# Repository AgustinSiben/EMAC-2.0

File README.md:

# EMAC-2.0
En este repositorio se encuentra contenido todo lo relacionado a la versión 2.0 del adquisidor de datos para EMAC (Estación de monitoreo ambiental costera)

Este repositorio se encuentra en desarrollo, se subiran las actualizaciones a medida que se avance en el mismo.

Ante cualquier consulta envíe un mail a la dirección: agustinsiben@gmail.com

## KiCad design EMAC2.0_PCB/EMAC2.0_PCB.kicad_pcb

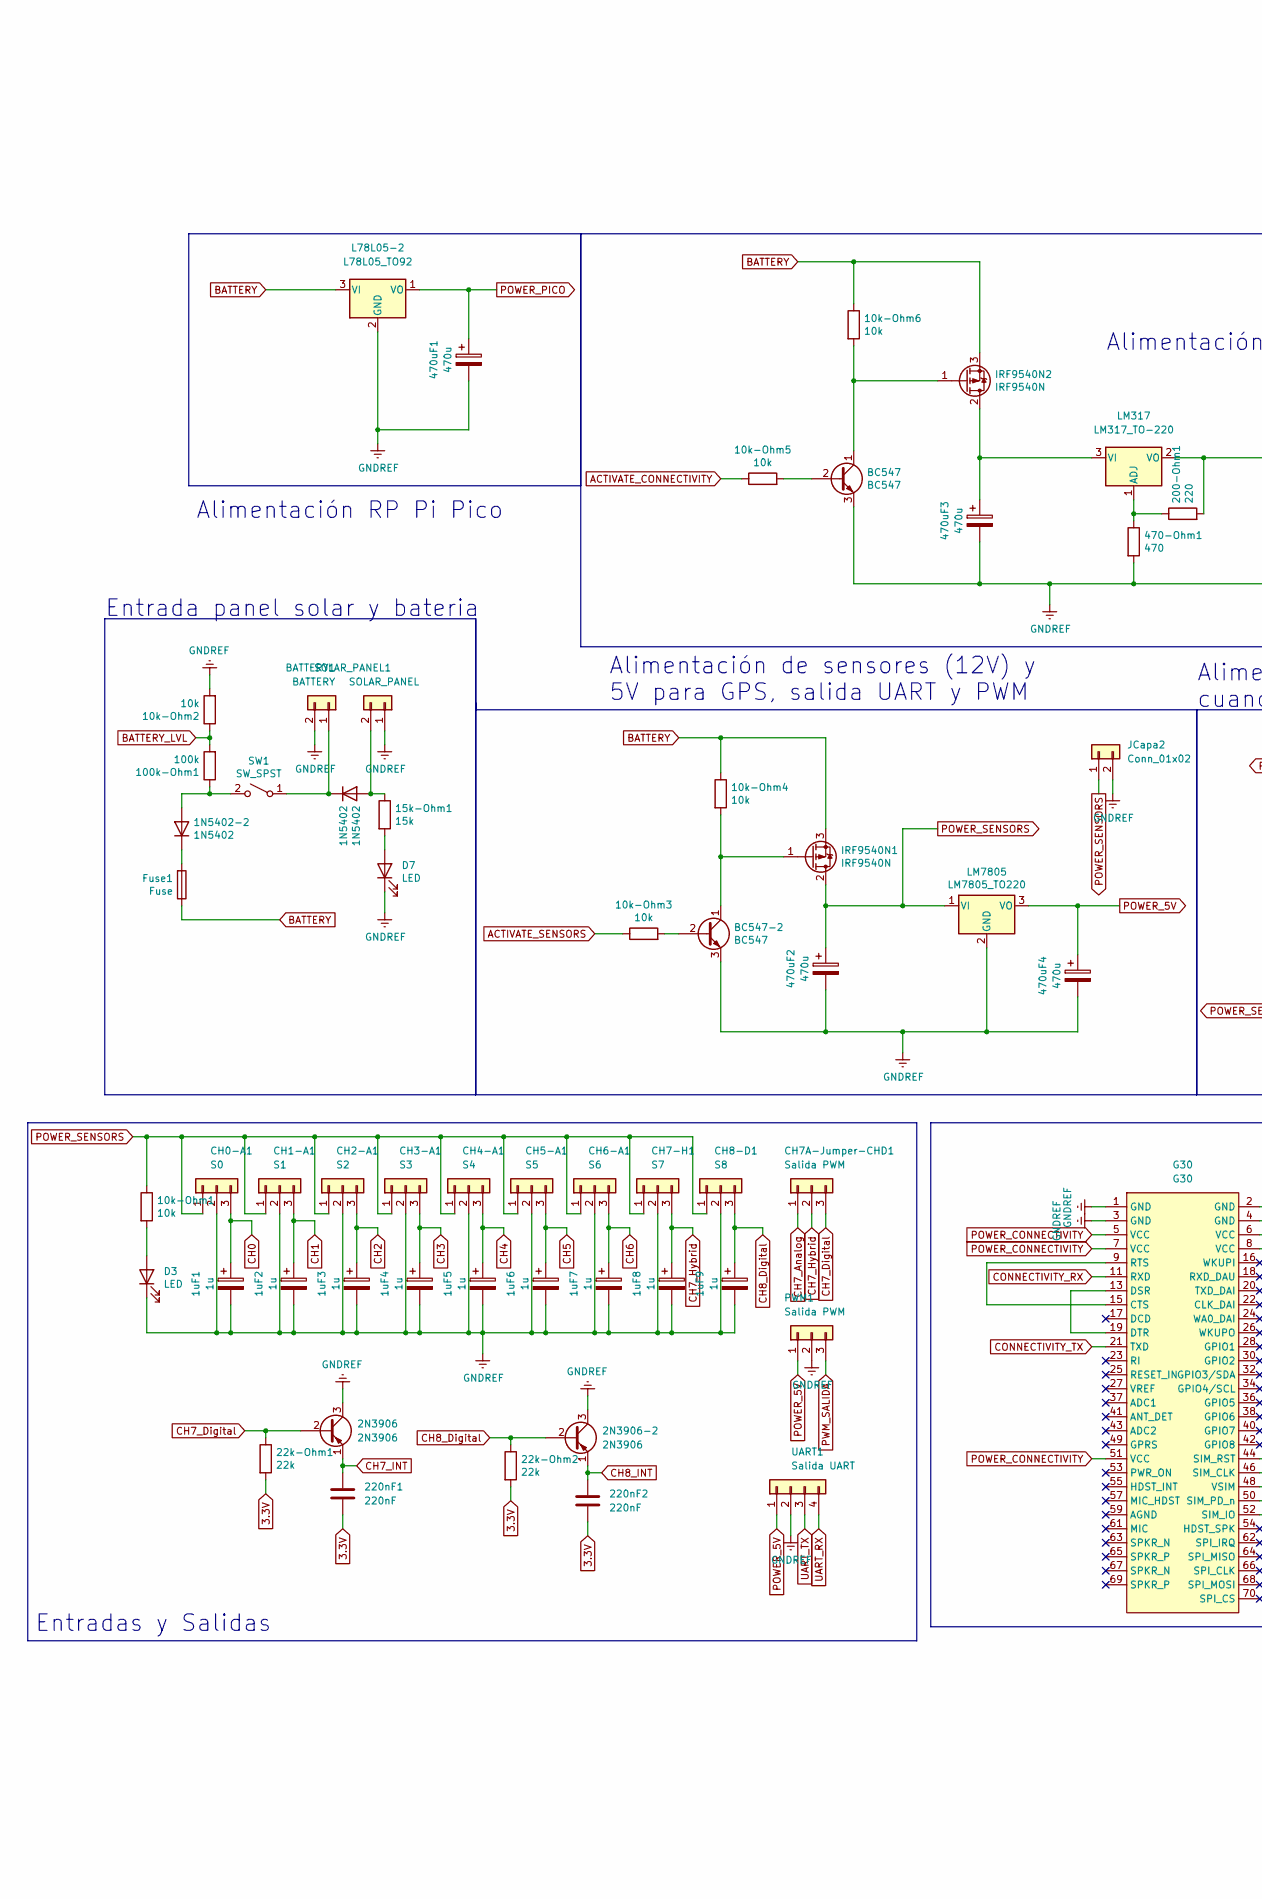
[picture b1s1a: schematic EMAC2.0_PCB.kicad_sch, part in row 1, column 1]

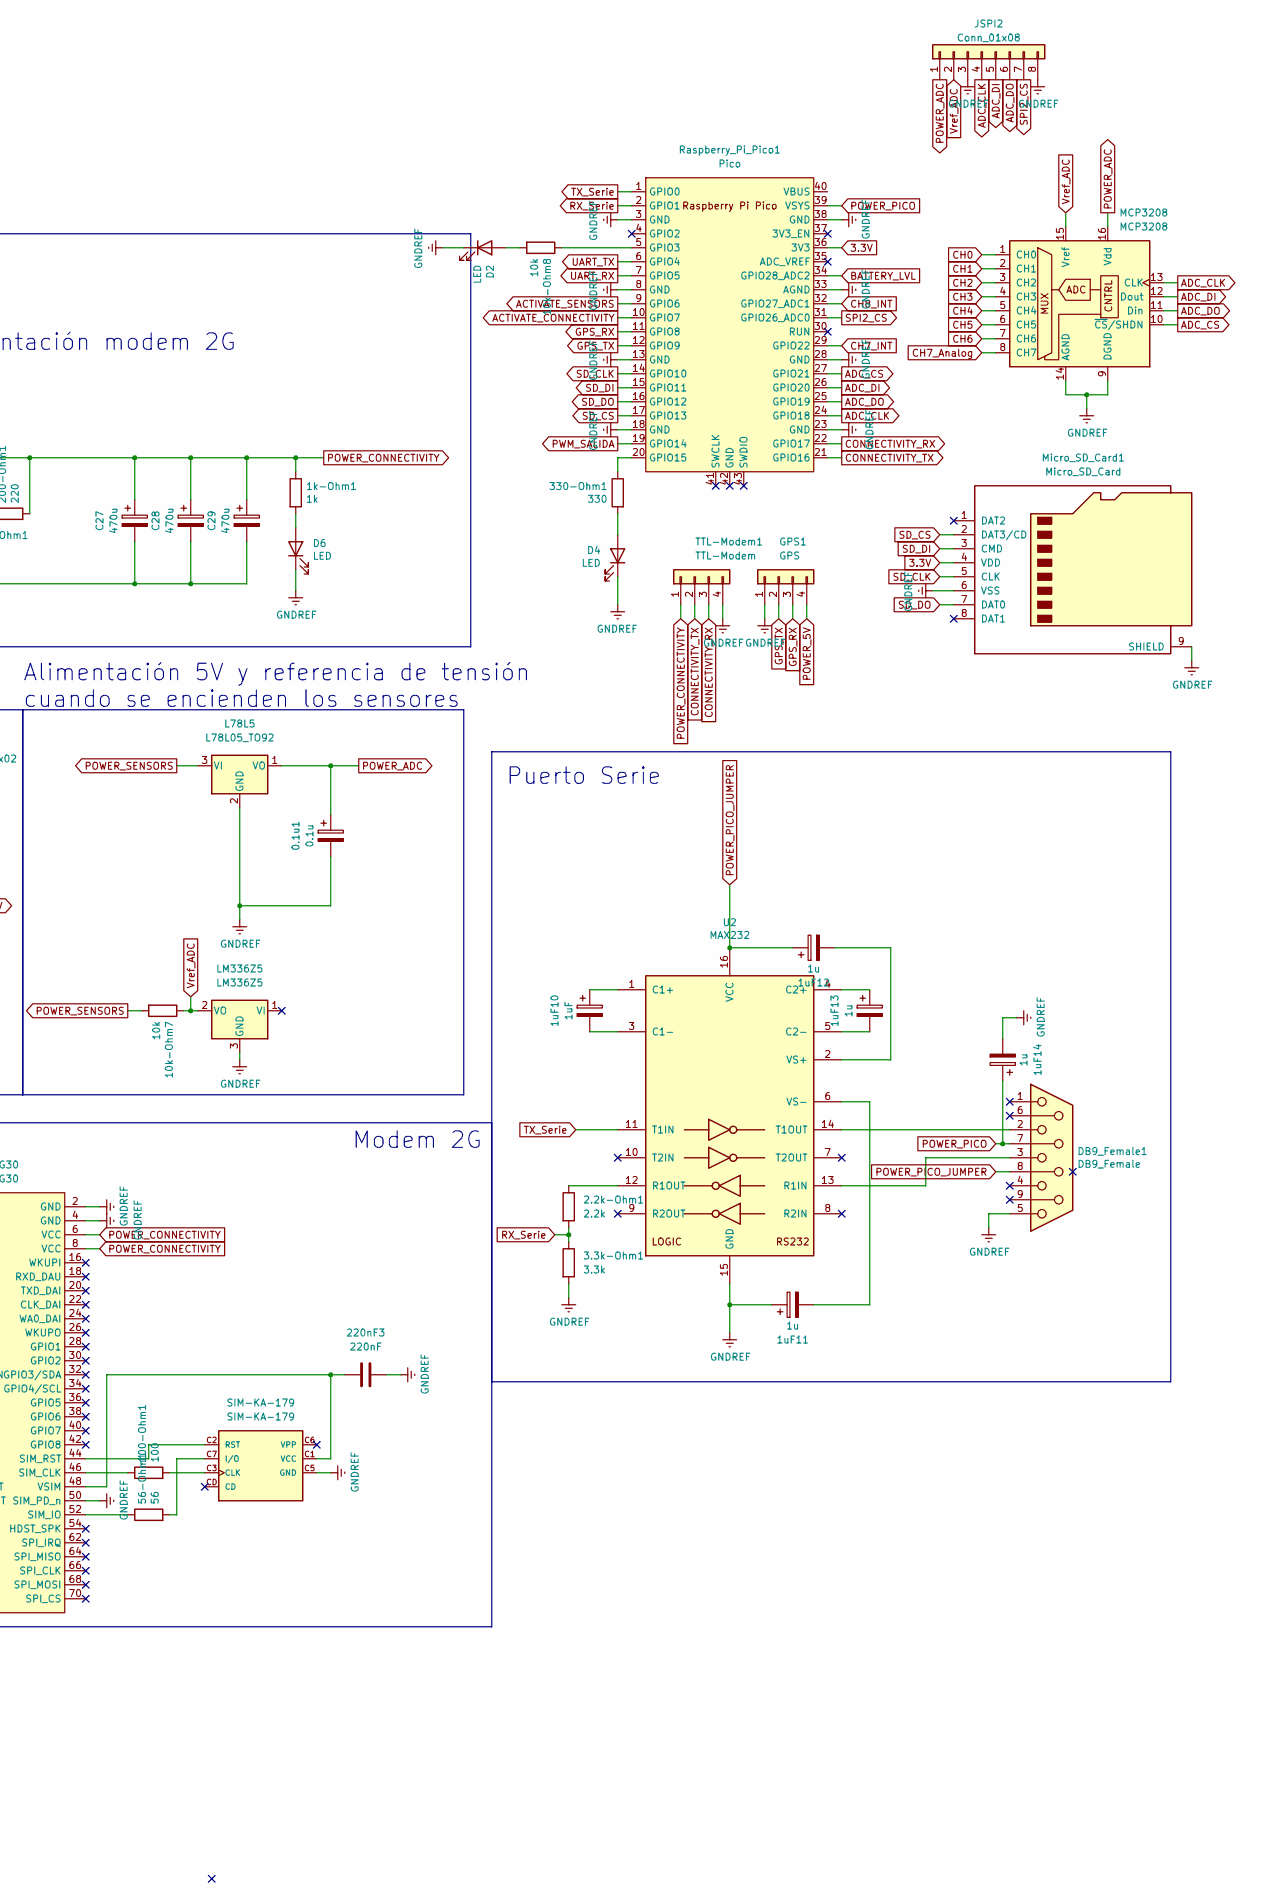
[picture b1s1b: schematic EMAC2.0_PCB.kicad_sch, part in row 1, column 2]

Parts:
0.1u1: 0.1u; CP_Radial_D5.0mm_P2.50mm
1N5402, 1N5402-2: 1N5402; D_DO-201AD_P15.24mm_Horizontal
1k-Ohm1: 1k; R_Axial_DIN0207_L6.3mm_D2.5mm_P10.16mm_Horizontal
1uF1, 1uF2, 1uF3, 1uF4, 1uF5, 1uF6, 1uF7, 1uF8, 1uF9, 1uF11, 1uF12, 1uF13, 1uF14: 1u; CP_Radial_D5.0mm_P2.50mm
1uF10: 1uF; CP_Radial_D5.0mm_P2.50mm
2.2k-Ohm1: 2.2k; R_Axial_DIN0207_L6.3mm_D2.5mm_P10.16mm_Horizontal
2N3906, 2N3906-2: 2N3906; TO-92_Inline_Wide
3.3k-Ohm1: 3.3k; R_Axial_DIN0207_L6.3mm_D2.5mm_P10.16mm_Horizontal
10k-Ohm1, 10k-Ohm2, 10k-Ohm3, 10k-Ohm4, 10k-Ohm5, 10k-Ohm6, 10k-Ohm7, 10k-Ohm8: 10k; R_Axial_DIN0207_L6.3mm_D2.5mm_P10.16mm_Horizontal
15k-Ohm1: 15k; R_Axial_DIN0207_L6.3mm_D2.5mm_P10.16mm_Horizontal
22k-Ohm1, 22k-Ohm2: 22k; R_Axial_DIN0207_L6.3mm_D2.5mm_P10.16mm_Horizontal
56-Ohm1: 56; R_Axial_DIN0207_L6.3mm_D2.5mm_P10.16mm_Horizontal
100-Ohm1: 100; R_Axial_DIN0207_L6.3mm_D2.5mm_P10.16mm_Horizontal
100k-Ohm1: 100k; R_Axial_DIN0207_L6.3mm_D2.5mm_P10.16mm_Horizontal
200-Ohm1: 220; R_Axial_DIN0207_L6.3mm_D2.5mm_P10.16mm_Horizontal
220nF1, 220nF2, 220nF3: 220nF; C_Disc_D5.1mm_W3.2mm_P5.00mm
330-Ohm1: 330; R_Axial_DIN0207_L6.3mm_D2.5mm_P10.16mm_Horizontal
470-Ohm1: 470; R_Axial_DIN0207_L6.3mm_D2.5mm_P10.16mm_Horizontal
470uF1, 470uF2, 470uF3, 470uF4: 470u; CP_Radial_D8.0mm_P5.00mm
BATTERY1: BATTERY; PhoenixContact_MSTBA_2,5_2-G-5,08_1x02_P5.08mm_Horizontal_B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
BC547, BC547-2: BC547; TO-92_Inline_Wide
C27, C28, C29: 470u; CP_Radial_D8.0mm_P5.00mm
CH0-A1: S0; PhoenixContact_MSTBA_2,5_3-G-5,08_1x03_P5.08mm_Horizontal_B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
CH1-A1: S1; PhoenixContact_MSTBA_2,5_3-G-5,08_1x03_P5.08mm_Horizontal_B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
CH2-A1: S2; PhoenixContact_MSTBA_2,5_3-G-5,08_1x03_P5.08mm_Horizontal_B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
CH3-A1: S3; PhoenixContact_MSTBA_2,5_3-G-5,08_1x03_P5.08mm_Horizontal_B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
CH4-A1: S4; PhoenixContact_MSTBA_2,5_3-G-5,08_1x03_P5.08mm_Horizontal_B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
CH5-A1: S5; PhoenixContact_MSTBA_2,5_3-G-5,08_1x03_P5.08mm_Horizontal_B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
CH6-A1: S6; PhoenixContact_MSTBA_2,5_3-G-5,08_1x03_P5.08mm_Horizontal_B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
CH7-H1: S7; PhoenixContact_MSTBA_2,5_3-G-5,08_1x03_P5.08mm_Horizontal_B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
CH7A-Jumper-CHD1: Salida PWM; PinHeader_1x03_P2.54mm_Vertical
CH8-D1: S8; PhoenixContact_MSTBA_2,5_3-G-5,08_1x03_P5.08mm_Horizontal_B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
D2, D3, D4, D6, D7: LED; LED_D4.0mm
DB9_Female1: DB9_Female; DSUB-9_Female_Horizontal_P2.77x2.84mm_EdgePinOffset4.94mm_H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
Fuse1: Fuse; 20x5
G30: G30; Molex_SlimStack_52991-0708_2x35_P0.50mm_Vertical
GPS1: GPS; PinHeader_1x04_P2.54mm_Vertical
IRF9540N1, IRF9540N2: IRF9540N; TO-220-3_Vertical
JCapa2: Conn_01x02; PinHeader_1x02_P2.54mm_Vertical
JSPI2: Conn_01x08; PinHeader_1x08_P2.54mm_Vertical
L78L5, L78L05-2: L78L05_TO92; TO-92_Inline_Wide
LM317: LM317_TO-220; TO-220-3_Vertical
LM336Z5: LM336Z5; TO-92_Inline_Wide
LM7805: LM7805_TO220; TO-220-3_Vertical
MCP3208: MCP3208; DIP-16_W7.62mm_Socket
Micro_SD_Card1: Micro_SD_Card; GCT-MEM2055-00-190-01-A
PWM1: Salida PWM; PhoenixContact_MSTBA_2,5_3-G-5,08_1x03_P5.08mm_Horizontal_B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
Raspberry_Pi_Pico1: Pico; RPi_Pico_SMD_TH
SIM-KA-179: SIM-KA-179; GCT_SIM7100-6-1-15-00-A_REVC; PARTREV C
SOLAR_PANEL1: SOLAR_PANEL; PhoenixContact_MSTBA_2,5_2-G-5,08_1x02_P5.08mm_Horizontal_B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
SW1: SW_SPST; SolderWire-0.75sqmm_1x02_P7mm_D1.25mm_OD3.5mm
TTL-Modem1: TTL-Modem; PinHeader_1x04_P2.54mm_Vertical
U2: MAX232; SOIC-16_3.9x9.9mm_P1.27mm
UART1: Salida UART; PhoenixContact_MSTBA_2,5_4-G-5,08_1x04_P5.08mm_Horizontal_B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

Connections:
3.3V: 22k-Ohm1.2, 22k-Ohm2.2, 220nF1.2, 220nF2.2, Micro_SD_Card1.4 (VDD), Raspberry_Pi_Pico1.36 (3V3)
ACTIVATE_CONNECTIVITY: 10k-Ohm5.1, Raspberry_Pi_Pico1.10 (GPIO7)
ACTIVATE_SENSORS: 10k-Ohm3.1, Raspberry_Pi_Pico1.9 (GPIO6)
ADC_CLK: JSPI2.4, MCP3208.13 (CLK), Raspberry_Pi_Pico1.24 (GPIO18)
ADC_CS: MCP3208.10 (~CS/SHDN), Raspberry_Pi_Pico1.27 (GPIO21)
ADC_DI: JSPI2.5, MCP3208.12 (Dout), Raspberry_Pi_Pico1.26 (GPIO20)
ADC_DO: JSPI2.6, MCP3208.11 (Din), Raspberry_Pi_Pico1.25 (GPIO19)
BATTERY: 10k-Ohm4.1, 10k-Ohm6.1, Fuse1.1, IRF9540N1.3 (S), IRF9540N2.3 (S), L78L05-2.3 (VI)
BATTERY_LVL: 10k-Ohm2.1, 100k-Ohm1.2, Raspberry_Pi_Pico1.34 (GPIO28_ADC2)
CH0: 1uF1.1, CH0-A1.3, MCP3208.1 (CH0)
CH1: 1uF2.1, CH1-A1.3, MCP3208.2 (CH1)
CH2: 1uF3.1, CH2-A1.3, MCP3208.3 (CH2)
CH3: 1uF4.1, CH3-A1.3, MCP3208.4 (CH3)
CH4: 1uF5.1, CH4-A1.3, MCP3208.5 (CH4)
CH5: 1uF6.1, CH5-A1.3, MCP3208.6 (CH5)
CH6: 1uF7.1, CH6-A1.3, MCP3208.7 (CH6)
CH7_Analog: CH7A-Jumper-CHD1.1, MCP3208.8 (CH7)
CH7_Digital: 2N3906.2 (B), 22k-Ohm1.1, CH7A-Jumper-CHD1.3
CH7_Hybrid: 1uF8.1, CH7-H1.3, CH7A-Jumper-CHD1.2
CH7_INT: 2N3906.1 (E), 220nF1.1, Raspberry_Pi_Pico1.29 (GPIO22)
CH8_Digital: 1uF9.1, 2N3906-2.2 (B), 22k-Ohm2.1, CH8-D1.3
CH8_INT: 2N3906-2.1 (E), 220nF2.1, Raspberry_Pi_Pico1.32 (GPIO27_ADC1)
CONNECTIVITY_RX: G30.11 (RXD), Raspberry_Pi_Pico1.22 (GPIO17), TTL-Modem1.3
CONNECTIVITY_TX: G30.21 (TXD), Raspberry_Pi_Pico1.21 (GPIO16), TTL-Modem1.2
GNDREF: 0.1u1.2, 1uF1.2, 1uF2.2, 1uF3.2, 1uF4.2, 1uF5.2, 1uF6.2, 1uF7.2, 1uF8.2, 1uF9.2, 1uF11.1, 1uF14.2, 2N3906.3 (C), 2N3906-2.3 (C), 3.3k-Ohm1.2, 10k-Ohm2.2, 220nF3.1, 470-Ohm1.2, 470uF1.2, 470uF2.2, 470uF3.2, 470uF4.2, BATTERY1.2, BC547.3 (E), BC547-2.3 (E), C27.2, C28.2, C29.2, CH0-A1.2, CH1-A1.2, CH2-A1.2, CH3-A1.2, CH4-A1.2, CH5-A1.2, CH6-A1.2, CH7-H1.2, CH8-D1.2, D2.1 (K), D3.1 (K), D4.1 (K), D6.1 (K), D7.1 (K), DB9_Female1.5, G30.1 (GND), G30.2 (GND), G30.3 (GND), G30.4 (GND), G30.50 (SIM_PD_n), GPS1.1, JCapa2.2, JSPI2.3, JSPI2.8, L78L5.2 (GND), L78L05-2.2 (GND), LM336Z5.3 (GND), LM7805.2 (GND), MCP3208.9 (DGND), MCP3208.14 (AGND), Micro_SD_Card1.6 (VSS), Micro_SD_Card1.9 (SHIELD), PWM1.2, Raspberry_Pi_Pico1.3 (GND), Raspberry_Pi_Pico1.8 (GND), Raspberry_Pi_Pico1.13 (GND), Raspberry_Pi_Pico1.18 (GND), Raspberry_Pi_Pico1.23 (GND), Raspberry_Pi_Pico1.28 (GND), Raspberry_Pi_Pico1.33 (AGND), Raspberry_Pi_Pico1.38 (GND), SIM-KA-179.C5 (GND), SOLAR_PANEL1.1, TTL-Modem1.4, U2.15 (GND), UART1.2
GPS_RX: GPS1.3, Raspberry_Pi_Pico1.11 (GPIO8)
GPS_TX: GPS1.2, Raspberry_Pi_Pico1.12 (GPIO9)
unnamed: 1N5402-2.1 (K), Fuse1.2
unnamed: 1N5402.1 (K), BATTERY1.1, SW1.1 (A)
unnamed: 1k-Ohm1.2, D6.2 (A)
unnamed: 1uF10.1, U2.1 (C1+)
unnamed: 1uF10.2, U2.3 (C1-)
unnamed: 1uF11.2, U2.6 (VS-)
unnamed: 1uF12.2, U2.2 (VS+)
unnamed: 1uF13.1, U2.4 (C2+)
unnamed: 1uF13.2, U2.5 (C2-)
unnamed: 2.2k-Ohm1.1, U2.12 (R1OUT)
unnamed: 10k-Ohm1.2, D3.2 (A)
unnamed: 10k-Ohm3.2, BC547-2.2 (B)
unnamed: 10k-Ohm4.2, BC547-2.1 (C), IRF9540N1.1 (G)
unnamed: 10k-Ohm5.2, BC547.2 (B)
unnamed: 10k-Ohm6.2, BC547.1 (C), IRF9540N2.1 (G)
unnamed: 10k-Ohm8.1, Raspberry_Pi_Pico1.5 (GPIO3)
unnamed: 10k-Ohm8.2, D2.2 (A)
unnamed: 1N5402.2 (A), 15k-Ohm1.1, SOLAR_PANEL1.2
unnamed: 15k-Ohm1.2, D7.2 (A)
unnamed: 56-Ohm1.1, G30.52 (SIM_IO)
unnamed: 56-Ohm1.2, SIM-KA-179.C7 (I/O)
unnamed: 100-Ohm1.1, G30.46 (SIM_CLK)
unnamed: 100-Ohm1.2, SIM-KA-179.C3 (CLK)
unnamed: 1N5402-2.2 (A), 100k-Ohm1.1, SW1.2 (B)
unnamed: 200-Ohm1.1, 470-Ohm1.1, LM317.1 (ADJ)
unnamed: 220nF3.2, G30.48 (VSIM), SIM-KA-179.C1 (VCC)
unnamed: 330-Ohm1.1, Raspberry_Pi_Pico1.20 (GPIO15)
unnamed: 330-Ohm1.2, D4.2 (A)
unnamed: 470uF3.1, IRF9540N2.2 (D), LM317.3 (VI)
unnamed: DB9_Female1.2, U2.14 (T1OUT)
unnamed: DB9_Female1.3, U2.13 (R1IN)
unnamed: G30.13 (DSR), G30.19 (DTR)
unnamed: G30.9 (RTS), G30.15 (CTS)
unnamed: G30.44 (SIM_RST), SIM-KA-179.C2 (RST)
POWER_5V: 470uF4.1, GPS1.4, LM7805.3 (VO), PWM1.1, UART1.1
POWER_ADC: 0.1u1.1, JSPI2.1, L78L5.1 (VO), MCP3208.16 (Vdd)
POWER_CONNECTIVITY: 1k-Ohm1.1, 200-Ohm1.2, C27.1, C28.1, C29.1, G30.5 (VCC), G30.6 (VCC), G30.7 (VCC), G30.8 (VCC), G30.51 (VCC), LM317.2 (VO), TTL-Modem1.1
POWER_PICO: 1uF14.1, 470uF1.1, DB9_Female1.7, L78L05-2.1 (VO), Raspberry_Pi_Pico1.39 (VSYS)
POWER_PICO_JUMPER: 1uF12.1, DB9_Female1.8, U2.16 (VCC)
POWER_SENSORS: 10k-Ohm1.1, 10k-Ohm7.2, 470uF2.1, CH0-A1.1, CH1-A1.1, CH2-A1.1, CH3-A1.1, CH4-A1.1, CH5-A1.1, CH6-A1.1, CH7-H1.1, CH8-D1.1, IRF9540N1.2 (D), JCapa2.1, L78L5.3 (VI), LM7805.1 (VI)
PWM_SALIDA: PWM1.3, Raspberry_Pi_Pico1.19 (GPIO14)
RX_Serie: 2.2k-Ohm1.2, 3.3k-Ohm1.1, Raspberry_Pi_Pico1.2 (GPIO1)
SD_CLK: Micro_SD_Card1.5 (CLK), Raspberry_Pi_Pico1.14 (GPIO10)
SD_CS: Micro_SD_Card1.2 (DAT3/CD), Raspberry_Pi_Pico1.17 (GPIO13)
SD_DI: Micro_SD_Card1.3 (CMD), Raspberry_Pi_Pico1.15 (GPIO11)
SD_DO: Micro_SD_Card1.7 (DAT0), Raspberry_Pi_Pico1.16 (GPIO12)
SPI2_CS: JSPI2.7, Raspberry_Pi_Pico1.31 (GPIO26_ADC0)
TX_Serie: Raspberry_Pi_Pico1.1 (GPIO0), U2.11 (T1IN)
UART_RX: Raspberry_Pi_Pico1.7 (GPIO5), UART1.4
UART_TX: Raspberry_Pi_Pico1.6 (GPIO4), UART1.3
Vref_ADC: 10k-Ohm7.1, JSPI2.2, LM336Z5.2 (VO), MCP3208.15 (Vref)

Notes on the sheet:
Modem 2G
Alimentación modem 2G
Alimentación 5V y referencia de tensión cuando se encienden los sensores
Entradas y Salidas
Entrada panel solar y bateria
Alimentación RP Pi Pico
Puerto Serie
Alimentación de sensores (12V) y 5V para GPS, salida UART y PWM

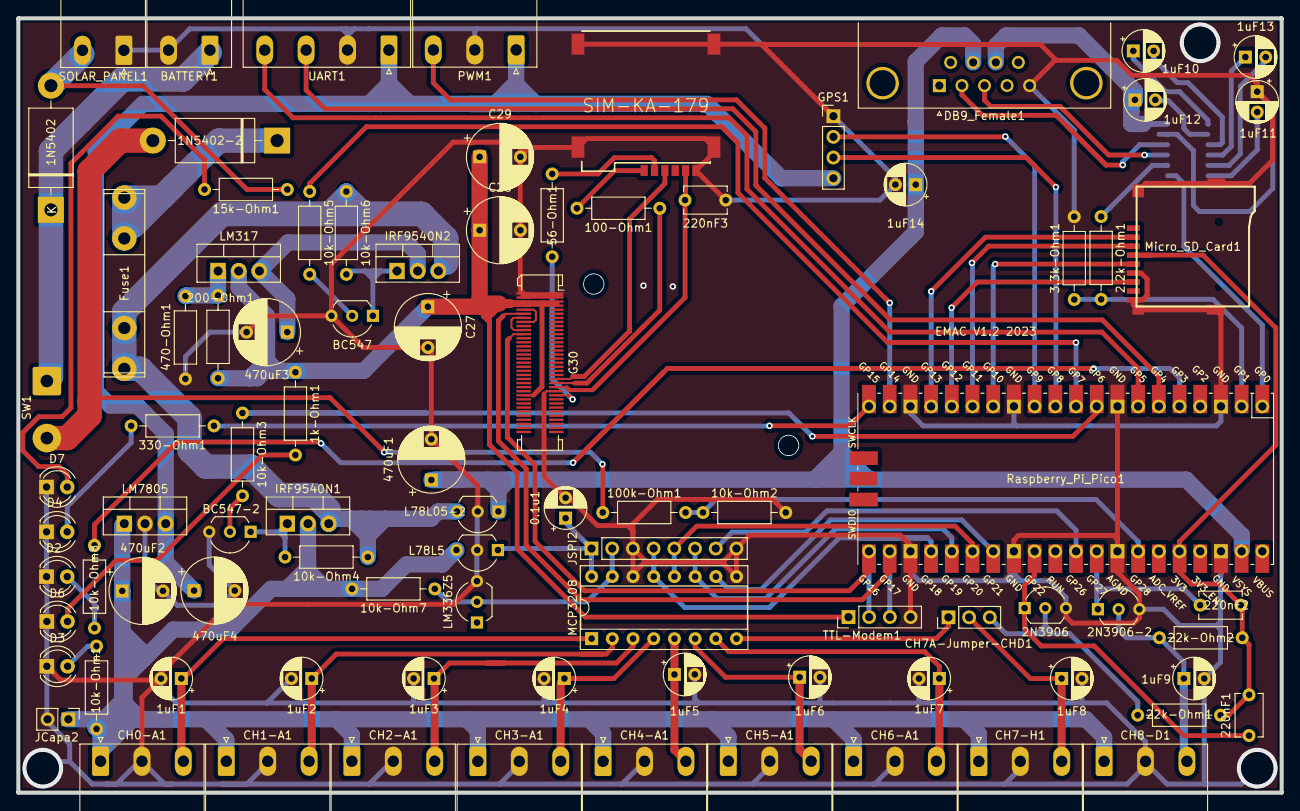
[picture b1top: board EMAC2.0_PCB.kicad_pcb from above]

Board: 2 copper layers, 155.0 x 95.0 mm, 90 parts (1 on the bottom side), 78 nets.

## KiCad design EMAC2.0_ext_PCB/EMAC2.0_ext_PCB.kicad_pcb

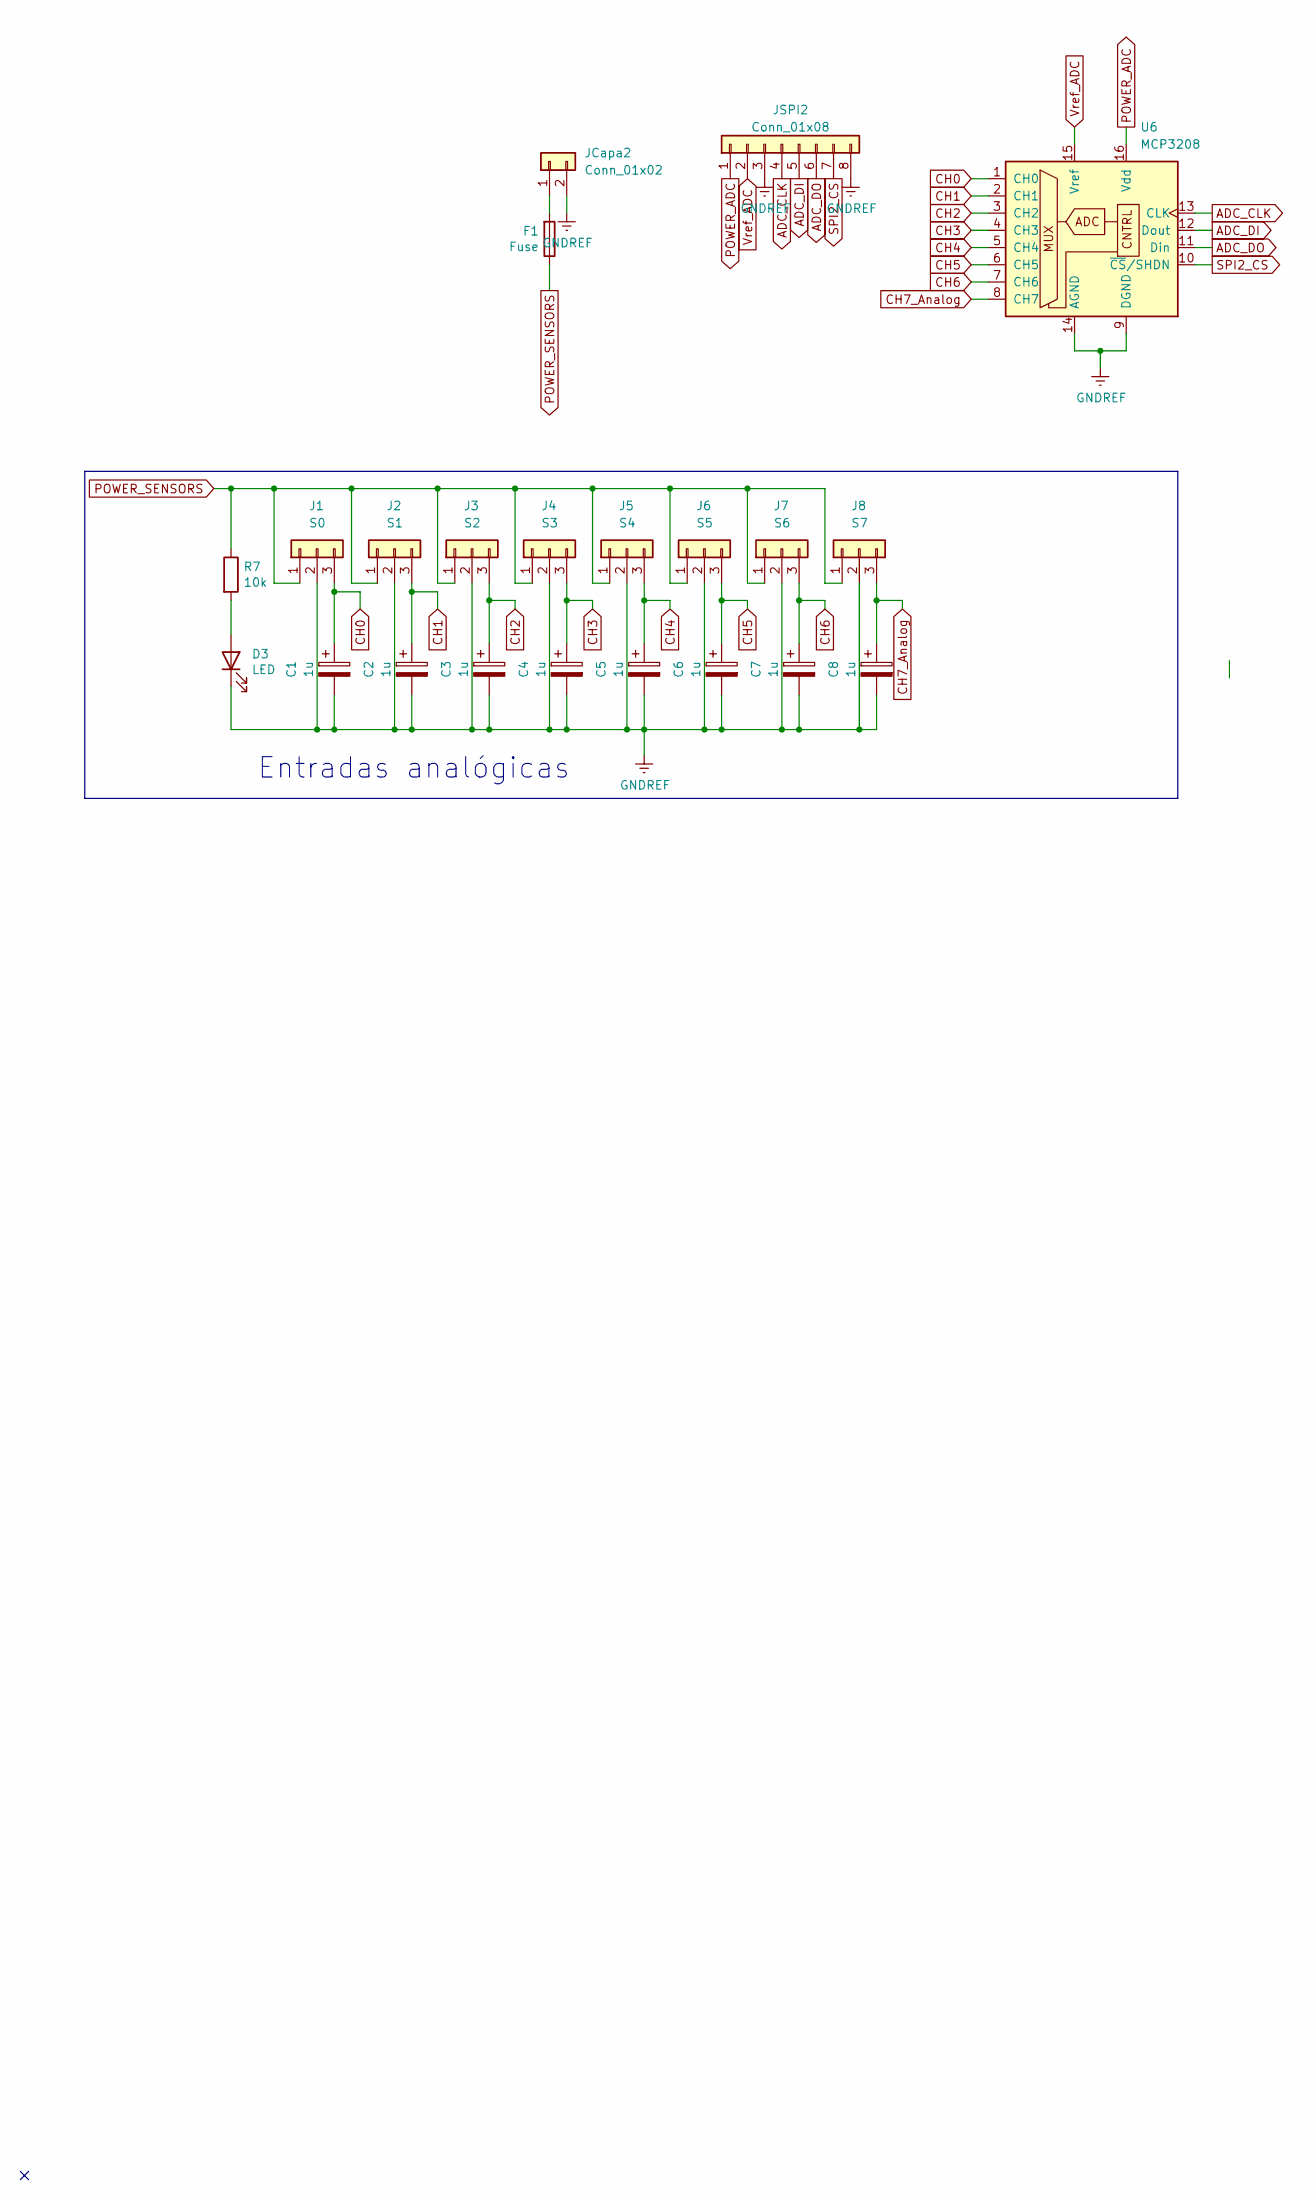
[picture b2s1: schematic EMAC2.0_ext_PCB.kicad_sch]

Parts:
C1, C2, C3, C4, C5, C6, C7, C8: 1u; CP_Radial_D5.0mm_P2.50mm
D3: LED; LED_D4.0mm
F1: Fuse; 20x5
J1: S0; PhoenixContact_MSTBA_2,5_3-G-5,08_1x03_P5.08mm_Horizontal_B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
J2: S1; PhoenixContact_MSTBA_2,5_3-G-5,08_1x03_P5.08mm_Horizontal_B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
J3: S2; PhoenixContact_MSTBA_2,5_3-G-5,08_1x03_P5.08mm_Horizontal_B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
J4: S3; PhoenixContact_MSTBA_2,5_3-G-5,08_1x03_P5.08mm_Horizontal_B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
J5: S4; PhoenixContact_MSTBA_2,5_3-G-5,08_1x03_P5.08mm_Horizontal_B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
J6: S5; PhoenixContact_MSTBA_2,5_3-G-5,08_1x03_P5.08mm_Horizontal_B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
J7: S6; PhoenixContact_MSTBA_2,5_3-G-5,08_1x03_P5.08mm_Horizontal_B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
J8: S7; PhoenixContact_MSTBA_2,5_3-G-5,08_1x03_P5.08mm_Horizontal_B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
JCapa2: Conn_01x02; PinHeader_1x02_P2.54mm_Vertical
JSPI2: Conn_01x08; PinHeader_1x08_P2.54mm_Vertical
R7: 10k; R_Axial_DIN0207_L6.3mm_D2.5mm_P10.16mm_Horizontal
U6: MCP3208; DIP-16_W7.62mm_Socket

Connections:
ADC_CLK: JSPI2.4, U6.13 (CLK)
ADC_DI: JSPI2.5, U6.12 (Dout)
ADC_DO: JSPI2.6, U6.11 (Din)
CH0: C1.1, J1.3, U6.1 (CH0)
CH1: C2.1, J2.3, U6.2 (CH1)
CH2: C3.1, J3.3, U6.3 (CH2)
CH3: C4.1, J4.3, U6.4 (CH3)
CH4: C5.1, J5.3, U6.5 (CH4)
CH5: C6.1, J6.3, U6.6 (CH5)
CH6: C7.1, J7.3, U6.7 (CH6)
CH7_Analog: C8.1, J8.3, U6.8 (CH7)
GNDREF: C1.2, C2.2, C3.2, C4.2, C5.2, C6.2, C7.2, C8.2, D3.1 (K), J1.2, J2.2, J3.2, J4.2, J5.2, J6.2, J7.2, J8.2, JCapa2.2, JSPI2.3, JSPI2.8, U6.9 (DGND), U6.14 (AGND)
unnamed: D3.2 (A), R7.2
unnamed: F1.2, JCapa2.1
POWER_ADC: JSPI2.1, U6.16 (Vdd)
POWER_SENSORS: F1.1, J1.1, J2.1, J3.1, J4.1, J5.1, J6.1, J7.1, J8.1, R7.1
SPI2_CS: JSPI2.7, U6.10 (~CS/SHDN)
Vref_ADC: JSPI2.2, U6.15 (Vref)

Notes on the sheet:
Entradas analógicas

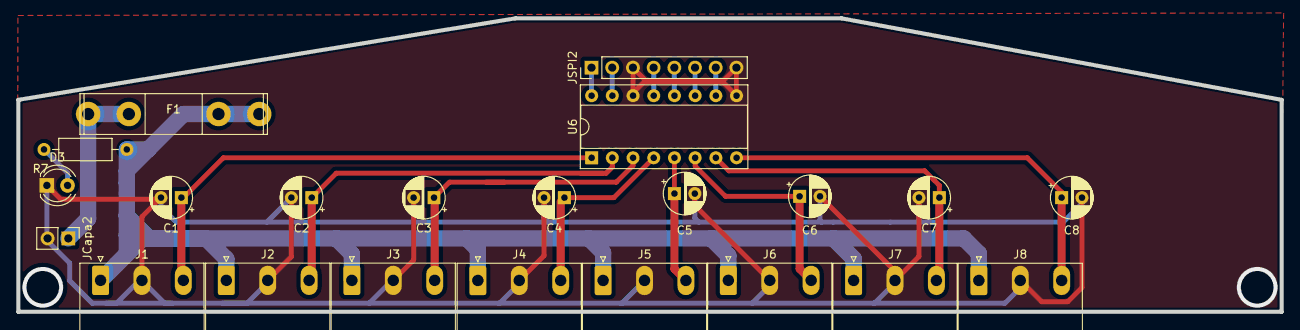
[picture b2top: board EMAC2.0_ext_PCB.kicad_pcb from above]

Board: 2 copper layers, 155.0 x 36.0 mm, 22 parts (0 on the bottom side), 18 nets.
